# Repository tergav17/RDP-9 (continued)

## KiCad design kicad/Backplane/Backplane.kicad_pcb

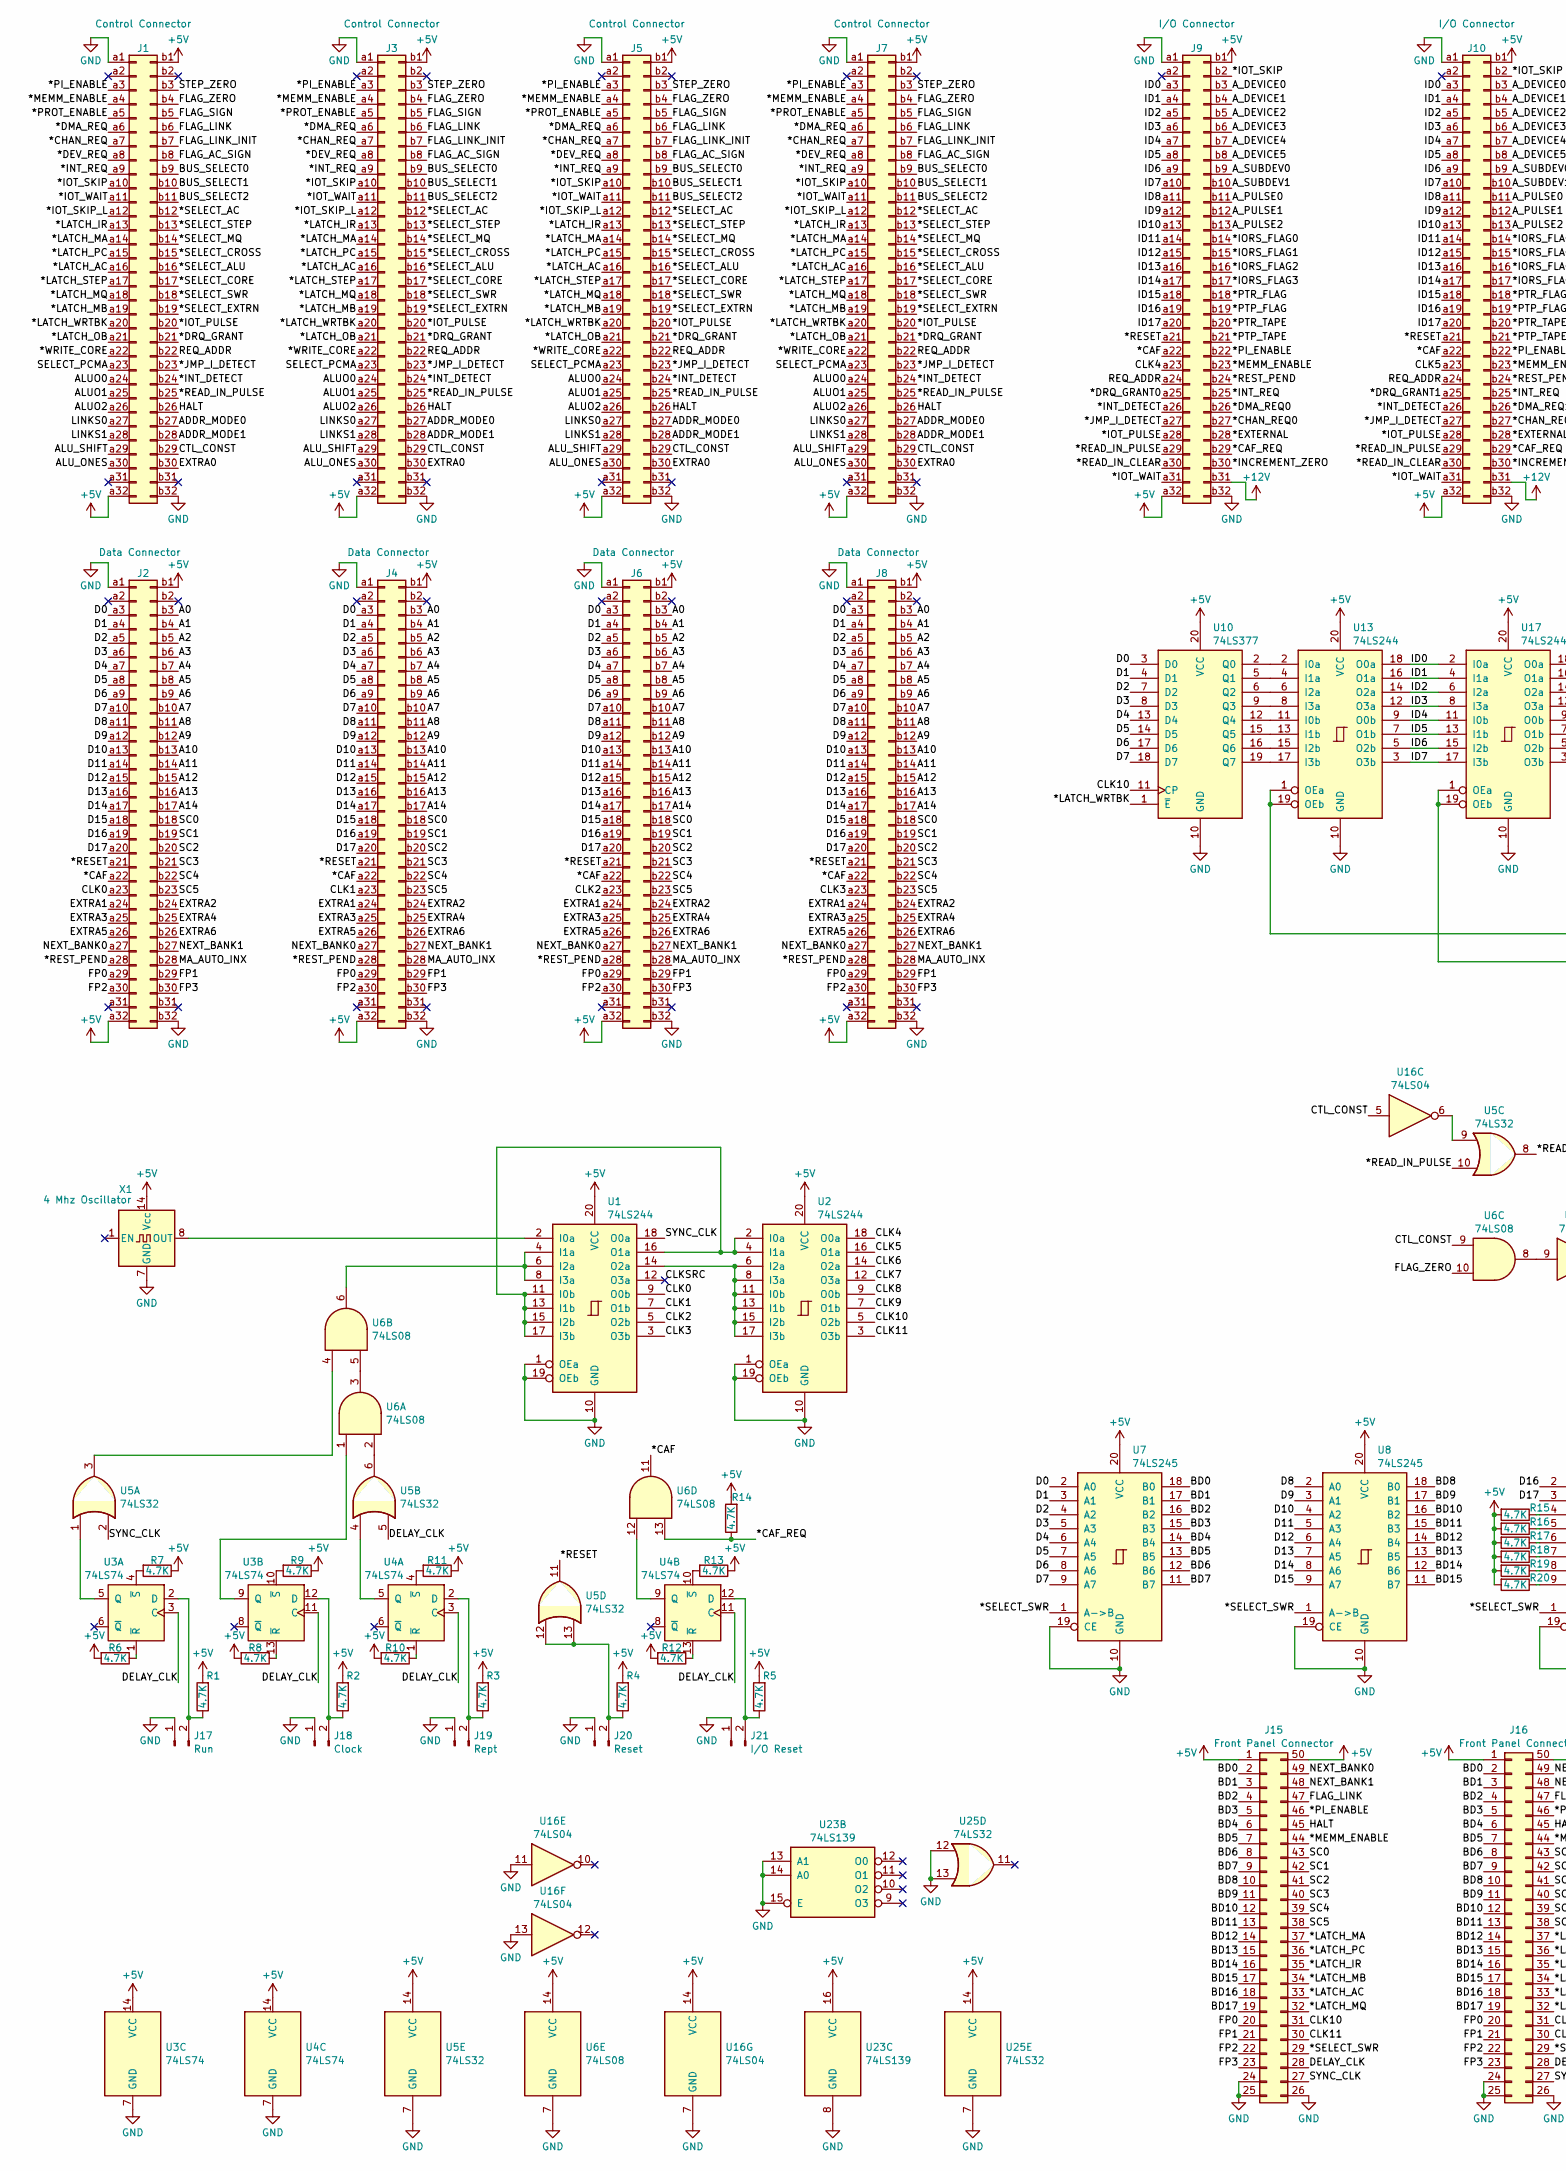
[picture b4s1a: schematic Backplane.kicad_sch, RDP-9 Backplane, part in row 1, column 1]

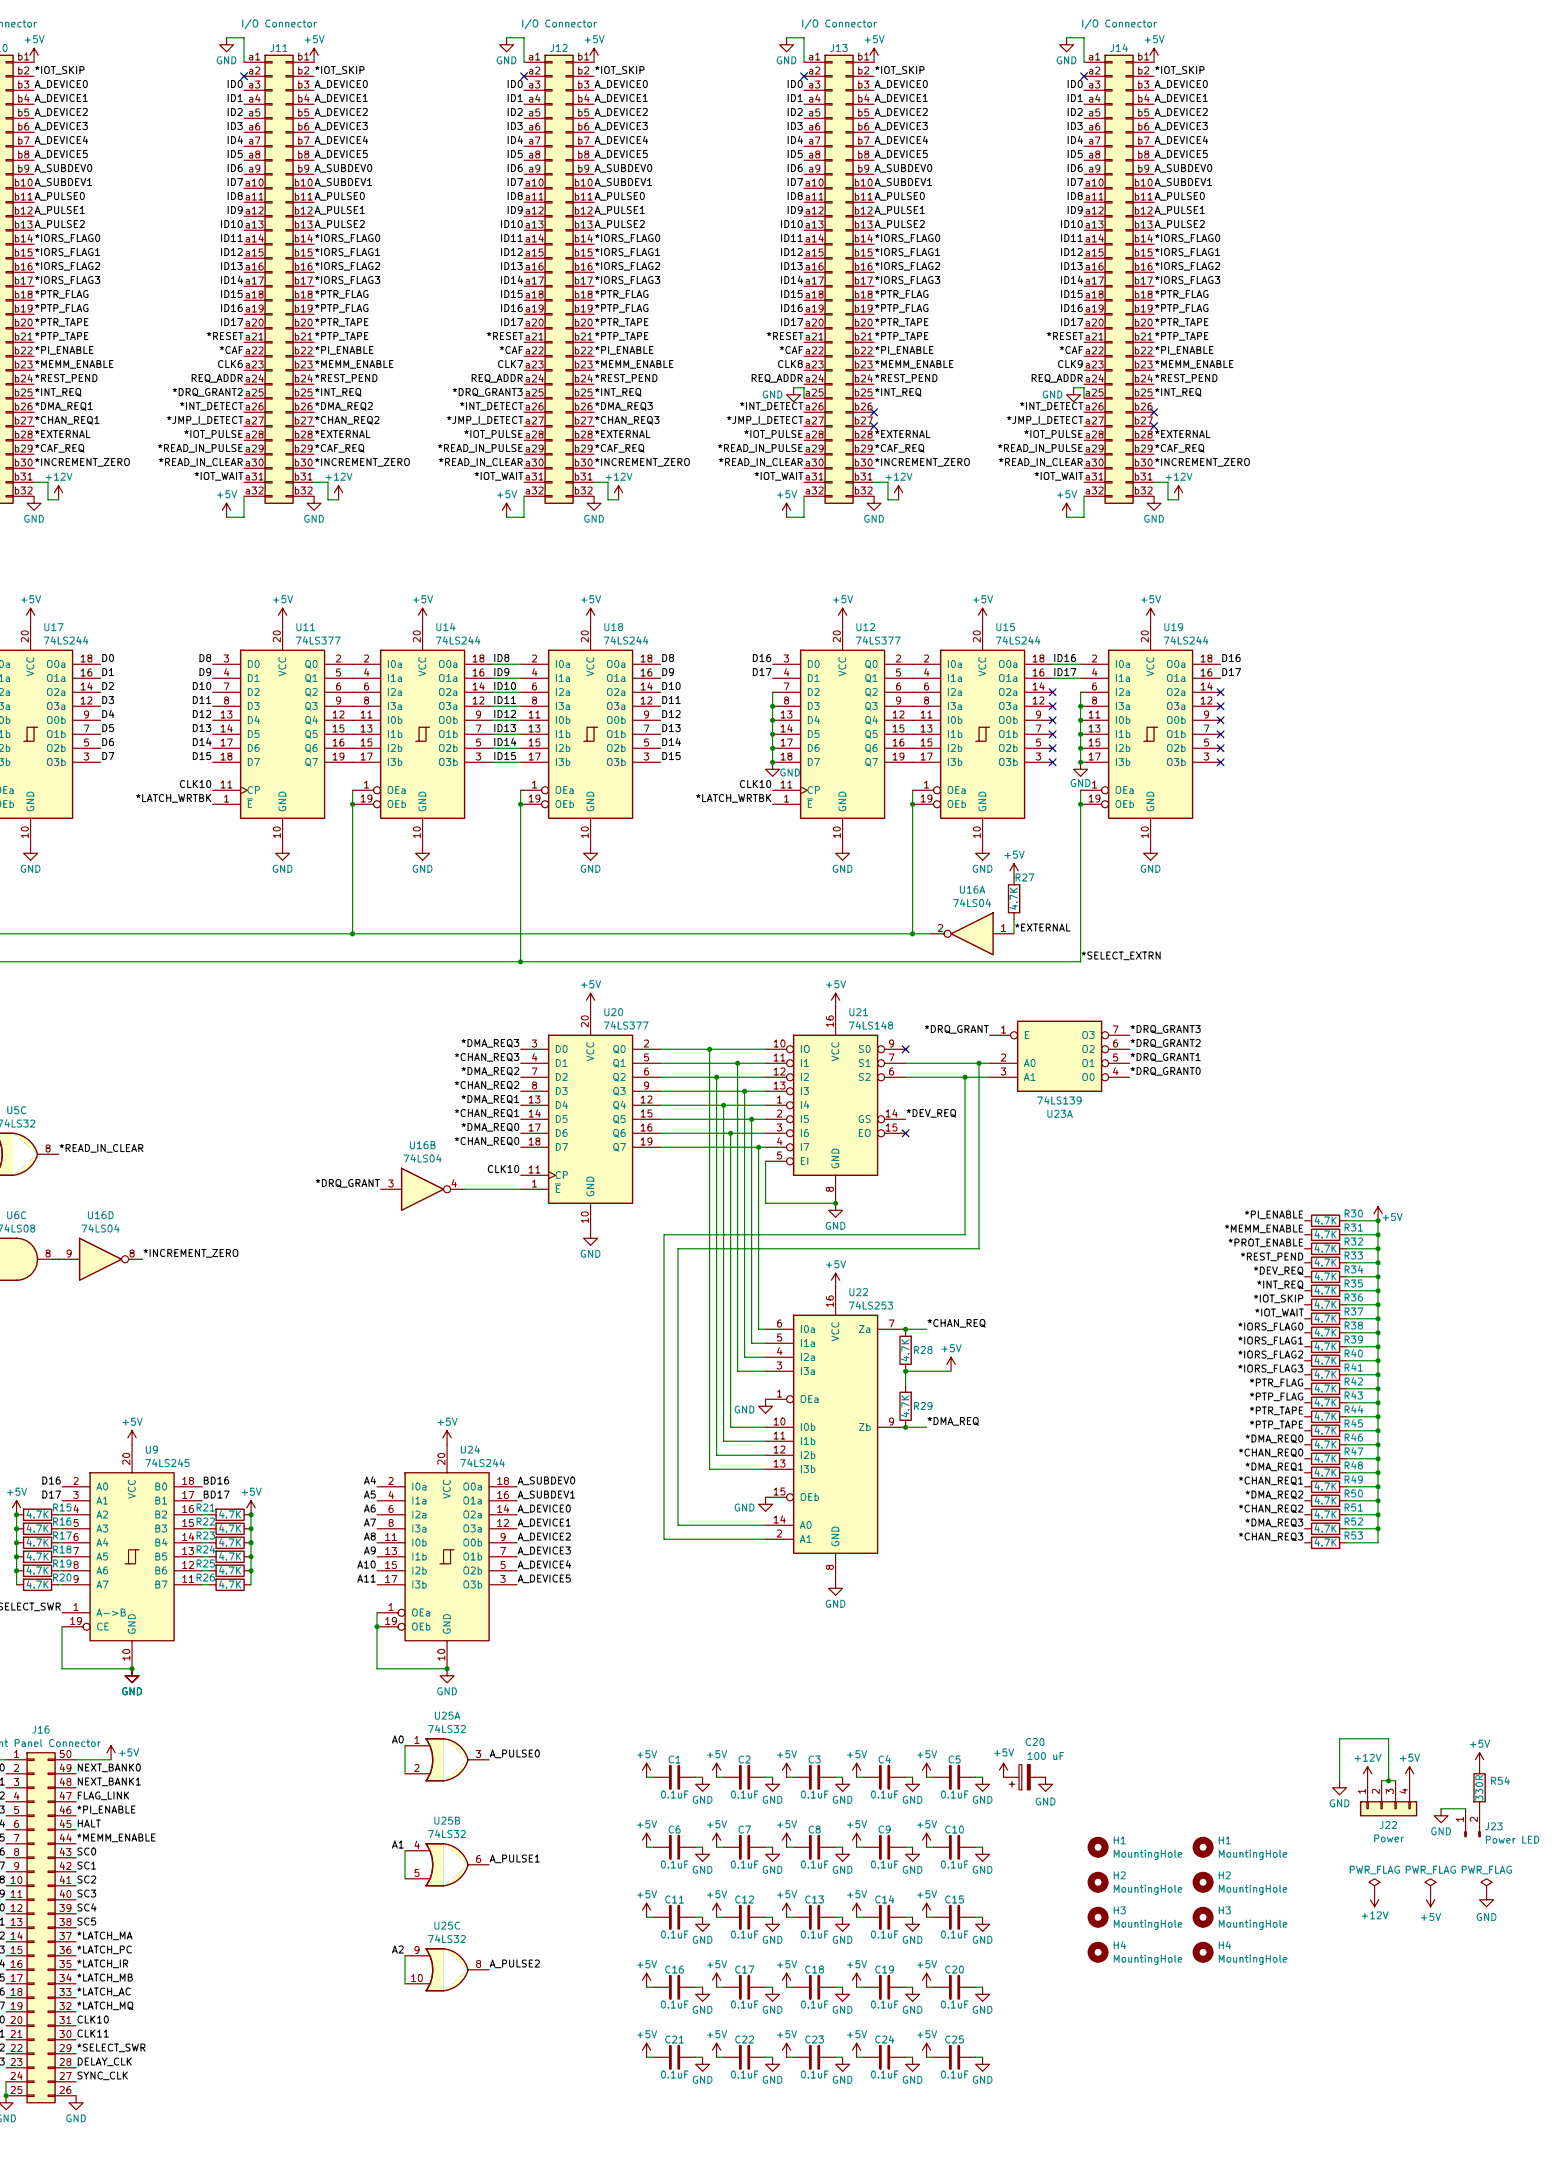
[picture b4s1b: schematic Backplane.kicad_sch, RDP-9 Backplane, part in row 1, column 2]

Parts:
C1, C2, C3, C4, C5, C6, C7, C8, C9, C10, C11, C12, C13, C14, C15, C16, C17, C18, C19, C20, C21, C22, C23, C24, C25: 0.1uF; C_Disc_D5.0mm_W2.5mm_P5.00mm
H1, H2, H3, H4: MountingHole; MountingHole_2.2mm_M2_Pad
J1, J3, J5, J7: Control Connector; DIN41612_B_2x32_Female_Vertical_THT
J2, J4, J6, J8: Data Connector; DIN41612_B_2x32_Female_Vertical_THT
J9, J10, J11, J12, J13, J14: I/O Connector; DIN41612_B_2x32_Female_Vertical_THT
J15, J16: Front Panel Connector; IDC-Header_2x25_P2.54mm_Vertical
J17: Run; PinHeader_1x02_P2.54mm_Vertical
J18: Clock; PinHeader_1x02_P2.54mm_Vertical
J19: Rept; PinHeader_1x02_P2.54mm_Vertical
J20: Reset; PinHeader_1x02_P2.54mm_Vertical
J21: I/O Reset; PinHeader_1x02_P2.54mm_Vertical
J22: Power; TE_MATE-N-LOK_350211-1_1x04_P5.08mm_Vertical
J23: Power LED; PinHeader_1x02_P2.54mm_Vertical
R1, R2, R3, R4, R5, R6, R7, R8, R9, R10, R11, R12, R13, R14, R15, R16, R17, R18, R19, R20, R21, R22, R23, R24, R25, R26, R27, R28, R29, R30, R31, R32, R33, R34, R35, R36, R37, R38, R39, R40, R41, R42, R43, R44, R45, R46, R47, R48, R49, R50, R51, R52, R53: 4.7K; R_Axial_DIN0207_L6.3mm_D2.5mm_P7.62mm_Horizontal
R54: 330R; R_Axial_DIN0207_L6.3mm_D2.5mm_P7.62mm_Horizontal
U1, U2, U13, U14, U15, U17, U18, U19, U24: 74LS244; DIP-20_W7.62mm
U3, U4: 74LS74; DIP-14_W7.62mm
U5, U25: 74LS32; DIP-14_W7.62mm
U6: 74LS08; DIP-14_W7.62mm
U7, U8, U9: 74LS245; DIP-20_W7.62mm
U10, U11, U12, U20: 74LS377; DIP-20_W7.62mm
U16: 74LS04; DIP-14_W7.62mm
U21: 74LS148; DIP-16_W7.62mm
U22: 74LS253; DIP-16_W7.62mm
U23: 74LS139; DIP-16_W7.62mm
X1: 4 Mhz Oscillator; Oscillator_DIP-14

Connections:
+5V: C1.1, C2.1, C3.1, C4.1, C5.1, C6.1, C7.1, C8.1, C9.1, C10.1, C11.1, C12.1, C13.1, C14.1, C15.1, C16.1, C17.1, C18.1, C19.1, C20.1, C21.1, C22.1, C23.1, C24.1, C25.1, J1.a32, J1.b1, J2.a32, J2.b1, J3.a32, J3.b1, J4.a32, J4.b1, J5.a32, J5.b1, J6.a32, J6.b1, J7.a32, J7.b1, J8.a32, J8.b1, J9.a32, J9.b1, J10.a32, J10.b1, J11.a32, J11.b1, J12.a32, J12.b1, J13.a32, J13.b1, J14.a32, J14.b1, J15.1, J15.50, J16.1, J16.50, J22.4, R1.2, R2.2, R3.2, R4.2, R5.2, R6.2, R7.1, R8.2, R9.1, R10.2, R11.1, R12.2, R13.1, R14.2, R15.2, R16.2, R17.2, R18.2, R19.2, R20.2, R21.1, R22.1, R23.1, R24.1, R25.1, R26.1, R27.2, R28.1, R29.2, R30.2, R31.2, R32.2, R33.2, R34.2, R35.2, R36.2, R37.2, R38.2, R39.2, R40.2, R41.2, R42.2, R43.2, R44.2, R45.2, R46.2, R47.2, R48.2, R49.2, R50.2, R51.2, R52.2, R53.2, R54.1, U1.20 (VCC), U2.20 (VCC), U3.14 (VCC), U4.14 (VCC), U5.14 (VCC), U6.14 (VCC), U7.20 (VCC), U8.20 (VCC), U9.20 (VCC), U10.20 (VCC), U11.20 (VCC), U12.20 (VCC), U13.20 (VCC), U14.20 (VCC), U15.20 (VCC), U16.14 (VCC), U17.20 (VCC), U18.20 (VCC), U19.20 (VCC), U20.20 (VCC), U21.16 (VCC), U22.16 (VCC), U23.16 (VCC), U24.20 (VCC), U25.14 (VCC), X1.14 (Vcc); also elsewhere on the board
+12V: J9.b31, J10.b31, J11.b31, J12.b31, J13.b31, J14.b31, J22.1
/*CAF: J2.a22, J4.a22, J6.a22, J8.a22, J9.a22, J10.a22, J11.a22, J12.a22, J13.a22, J14.a22, U6.11
/*CAF_REQ: J9.b29, J10.b29, J11.b29, J12.b29, J13.b29, J14.b29, R14.1, U6.13
/*CHAN_REQ: J1.a7, J3.a7, J5.a7, J7.a7, R28.2, U22.7 (Za)
/*CHAN_REQ0: J9.b27, R47.1, U20.18 (D7)
/*CHAN_REQ1: J10.b27, R49.1, U20.14 (D5)
/*CHAN_REQ2: J11.b27, R51.1, U20.8 (D3)
/*CHAN_REQ3: J12.b27, R53.1, U20.4 (D1)
/*DEV_REQ: J1.a8, J3.a8, J5.a8, J7.a8, R34.1, U21.14 (GS)
/*DMA_REQ: J1.a6, J3.a6, J5.a6, J7.a6, R29.1, U22.9 (Zb)
/*DMA_REQ0: J9.b26, R46.1, U20.17 (D6)
/*DMA_REQ1: J10.b26, R48.1, U20.13 (D4)
/*DMA_REQ2: J11.b26, R50.1, U20.7 (D2)
/*DMA_REQ3: J12.b26, R52.1, U20.3 (D0)
/*DRQ_GRANT: J1.b21, J3.b21, J5.b21, J7.b21, U16.3, U23.1 (E)
/*DRQ_GRANT0: J9.a25, U23.4 (O0)
/*DRQ_GRANT1: J10.a25, U23.5 (O1)
/*DRQ_GRANT2: J11.a25, U23.6 (O2)
/*DRQ_GRANT3: J12.a25, U23.7 (O3)
/*EXTERNAL: J9.b28, J10.b28, J11.b28, J12.b28, J13.b28, J14.b28, R27.1, U16.1
/*INCREMENT_ZERO: J9.b30, J10.b30, J11.b30, J12.b30, J13.b30, J14.b30, U16.8
/*INT_DETECT: J1.b24, J3.b24, J5.b24, J7.b24, J9.a26, J10.a26, J11.a26, J12.a26, J13.a26, J14.a26
/*INT_REQ: J1.a9, J3.a9, J5.a9, J7.a9, J9.b25, J10.b25, J11.b25, J12.b25, J13.b25, J14.b25, R35.1
/*IORS_FLAG0: J9.b14, J10.b14, J11.b14, J12.b14, J13.b14, J14.b14, R38.1
/*IORS_FLAG1: J9.b15, J10.b15, J11.b15, J12.b15, J13.b15, J14.b15, R39.1
/*IORS_FLAG2: J9.b16, J10.b16, J11.b16, J12.b16, J13.b16, J14.b16, R40.1
/*IORS_FLAG3: J9.b17, J10.b17, J11.b17, J12.b17, J13.b17, J14.b17, R41.1
/*IOT_PULSE: J1.b20, J3.b20, J5.b20, J7.b20, J9.a28, J10.a28, J11.a28, J12.a28, J13.a28, J14.a28
/*IOT_SKIP: J1.a10, J3.a10, J5.a10, J7.a10, J9.b2, J10.b2, J11.b2, J12.b2, J13.b2, J14.b2, R36.1
/*IOT_SKIP_L: J1.a12, J3.a12, J5.a12, J7.a12
/*IOT_WAIT: J1.a11, J3.a11, J5.a11, J7.a11, J9.a31, J10.a31, J11.a31, J12.a31, J13.a31, J14.a31, R37.1
/*JMP_I_DETECT: J1.b23, J3.b23, J5.b23, J7.b23, J9.a27, J10.a27, J11.a27, J12.a27, J13.a27, J14.a27
/*LATCH_AC: J1.a16, J3.a16, J5.a16, J7.a16, J15.33, J16.33
/*LATCH_IR: J1.a13, J3.a13, J5.a13, J7.a13, J15.35, J16.35
/*LATCH_MA: J1.a14, J3.a14, J5.a14, J7.a14, J15.37, J16.37
/*LATCH_MB: J1.a19, J3.a19, J5.a19, J7.a19, J15.34, J16.34
/*LATCH_MQ: J1.a18, J3.a18, J5.a18, J7.a18, J15.32, J16.32
/*LATCH_OB: J1.a21, J3.a21, J5.a21, J7.a21
/*LATCH_PC: J1.a15, J3.a15, J5.a15, J7.a15, J15.36, J16.36
/*LATCH_STEP: J1.a17, J3.a17, J5.a17, J7.a17
/*LATCH_WRTBK: J1.a20, J3.a20, J5.a20, J7.a20, U10.1 (~E), U11.1 (~E), U12.1 (~E)
/*MEMM_ENABLE: J1.a4, J3.a4, J5.a4, J7.a4, J9.b23, J10.b23, J11.b23, J12.b23, J13.b23, J14.b23, J15.44, J16.44, R31.1
/*PI_ENABLE: J1.a3, J3.a3, J5.a3, J7.a3, J9.b22, J10.b22, J11.b22, J12.b22, J13.b22, J14.b22, J15.46, J16.46, R30.1
/*PROT_ENABLE: J1.a5, J3.a5, J5.a5, J7.a5, R32.1
/*PTP_FLAG: J9.b19, J10.b19, J11.b19, J12.b19, J13.b19, J14.b19, R43.1
/*PTP_TAPE: J9.b21, J10.b21, J11.b21, J12.b21, J13.b21, J14.b21, R45.1
/*PTR_FLAG: J9.b18, J10.b18, J11.b18, J12.b18, J13.b18, J14.b18, R42.1
/*PTR_TAPE: J9.b20, J10.b20, J11.b20, J12.b20, J13.b20, J14.b20, R44.1
/*READ_IN_CLEAR: J9.a30, J10.a30, J11.a30, J12.a30, J13.a30, J14.a30, U5.8
/*READ_IN_PULSE: J1.b25, J3.b25, J5.b25, J7.b25, J9.a29, J10.a29, J11.a29, J12.a29, J13.a29, J14.a29, U5.10
/*RESET: J2.a21, J4.a21, J6.a21, J8.a21, J9.a21, J10.a21, J11.a21, J12.a21, J13.a21, J14.a21, U5.11
/*REST_PEND: J2.a28, J4.a28, J6.a28, J8.a28, J9.b24, J10.b24, J11.b24, J12.b24, J13.b24, J14.b24, R33.1
/*SELECT_AC: J1.b12, J3.b12, J5.b12, J7.b12
/*SELECT_ALU: J1.b16, J3.b16, J5.b16, J7.b16
/*SELECT_CORE: J1.b17, J3.b17, J5.b17, J7.b17
/*SELECT_CROSS: J1.b15, J3.b15, J5.b15, J7.b15
/*SELECT_EXTRN: J1.b19, J3.b19, J5.b19, J7.b19, U17.1 (OEa), U17.19 (OEb), U18.1 (OEa), U18.19 (OEb), U19.1 (OEa), U19.19 (OEb)
/*SELECT_MQ: J1.b14, J3.b14, J5.b14, J7.b14
/*SELECT_STEP: J1.b13, J3.b13, J5.b13, J7.b13
/*SELECT_SWR: J1.b18, J3.b18, J5.b18, J7.b18, J15.29, J16.29, U7.1 (A->B), U8.1 (A->B), U9.1 (A->B)
/*WRITE_CORE: J1.a22, J3.a22, J5.a22, J7.a22
/A0: J2.b3, J4.b3, J6.b3, J8.b3, U25.1, U25.2
/A1: J2.b4, J4.b4, J6.b4, J8.b4, U25.4, U25.5
/A2: J2.b5, J4.b5, J6.b5, J8.b5, U25.9, U25.10
/A3: J2.b6, J4.b6, J6.b6, J8.b6
/A4: J2.b7, J4.b7, J6.b7, J8.b7, U24.2 (I0a)
/A5: J2.b8, J4.b8, J6.b8, J8.b8, U24.4 (I1a)
/A6: J2.b9, J4.b9, J6.b9, J8.b9, U24.6 (I2a)
/A7: J2.b10, J4.b10, J6.b10, J8.b10, U24.8 (I3a)
/A8: J2.b11, J4.b11, J6.b11, J8.b11, U24.11 (I0b)
/A9: J2.b12, J4.b12, J6.b12, J8.b12, U24.13 (I1b)
/A10: J2.b13, J4.b13, J6.b13, J8.b13, U24.15 (I2b)
/A11: J2.b14, J4.b14, J6.b14, J8.b14, U24.17 (I3b)
/A12: J2.b15, J4.b15, J6.b15, J8.b15
/A13: J2.b16, J4.b16, J6.b16, J8.b16
/A14: J2.b17, J4.b17, J6.b17, J8.b17
/ADDR_MODE0: J1.b27, J3.b27, J5.b27, J7.b27
/ADDR_MODE1: J1.b28, J3.b28, J5.b28, J7.b28
/ALUO0: J1.a24, J3.a24, J5.a24, J7.a24
/ALUO1: J1.a25, J3.a25, J5.a25, J7.a25
/ALUO2: J1.a26, J3.a26, J5.a26, J7.a26
/ALU_ONES: J1.a30, J3.a30, J5.a30, J7.a30
/ALU_SHIFT: J1.a29, J3.a29, J5.a29, J7.a29
/A_DEVICE0: J9.b3, J10.b3, J11.b3, J12.b3, J13.b3, J14.b3, U24.14 (O2a)
/A_DEVICE1: J9.b4, J10.b4, J11.b4, J12.b4, J13.b4, J14.b4, U24.12 (O3a)
/A_DEVICE2: J9.b5, J10.b5, J11.b5, J12.b5, J13.b5, J14.b5, U24.9 (O0b)
/A_DEVICE3: J9.b6, J10.b6, J11.b6, J12.b6, J13.b6, J14.b6, U24.7 (O1b)
/A_DEVICE4: J9.b7, J10.b7, J11.b7, J12.b7, J13.b7, J14.b7, U24.5 (O2b)
/A_DEVICE5: J9.b8, J10.b8, J11.b8, J12.b8, J13.b8, J14.b8, U24.3 (O3b)
/A_PULSE0: J9.b11, J10.b11, J11.b11, J12.b11, J13.b11, J14.b11, U25.3
/A_PULSE1: J9.b12, J10.b12, J11.b12, J12.b12, J13.b12, J14.b12, U25.6
/A_PULSE2: J9.b13, J10.b13, J11.b13, J12.b13, J13.b13, J14.b13, U25.8
/A_SUBDEV0: J9.b9, J10.b9, J11.b9, J12.b9, J13.b9, J14.b9, U24.18 (O0a)
/A_SUBDEV1: J9.b10, J10.b10, J11.b10, J12.b10, J13.b10, J14.b10, U24.16 (O1a)
/BD0: J15.2, J16.2, U7.18 (B0)
/BD1: J15.3, J16.3, U7.17 (B1)
/BD2: J15.4, J16.4, U7.16 (B2)
/BD3: J15.5, J16.5, U7.15 (B3)
/BD4: J15.6, J16.6, U7.14 (B4)
/BD5: J15.7, J16.7, U7.13 (B5)
/BD6: J15.8, J16.8, U7.12 (B6)
/BD7: J15.9, J16.9, U7.11 (B7)
/BD8: J15.10, J16.10, U8.18 (B0)
/BD9: J15.11, J16.11, U8.17 (B1)
/BD10: J15.12, J16.12, U8.16 (B2)
/BD11: J15.13, J16.13, U8.15 (B3)
/BD12: J15.14, J16.14, U8.14 (B4)
/BD13: J15.15, J16.15, U8.13 (B5)
/BD14: J15.16, J16.16, U8.12 (B6)
/BD15: J15.17, J16.17, U8.11 (B7)
/BD16: J15.18, J16.18, U9.18 (B0)
/BD17: J15.19, J16.19, U9.17 (B1)
/BUS_SELECT0: J1.b9, J3.b9, J5.b9, J7.b9
/BUS_SELECT1: J1.b10, J3.b10, J5.b10, J7.b10
/BUS_SELECT2: J1.b11, J3.b11, J5.b11, J7.b11
/CLK0: J2.a23, U1.9 (O0b)
/CLK1: J4.a23, U1.7 (O1b)
/CLK2: J6.a23, U1.5 (O2b)
/CLK3: J8.a23, U1.3 (O3b)
/CLK4: J9.a23, U2.18 (O0a)
/CLK5: J10.a23, U2.16 (O1a)
/CLK6: J11.a23, U2.14 (O2a)
/CLK7: J12.a23, U2.12 (O3a)
/CLK8: J13.a23, U2.9 (O0b)
/CLK9: J14.a23, U2.7 (O1b)
/CLK10: J15.31, J16.31, U2.5 (O2b), U10.11 (CP), U11.11 (CP), U12.11 (CP), U20.11 (CP)
/CLK11: J15.30, J16.30, U2.3 (O3b)
/CLKSRC: U1.12 (O3a)
/CTL_CONST: J1.b29, J3.b29, J5.b29, J7.b29, U6.9, U16.5
/D0: J2.a3, J4.a3, J6.a3, J8.a3, U7.2 (A0), U10.3 (D0), U17.18 (O0a)
/D1: J2.a4, J4.a4, J6.a4, J8.a4, U7.3 (A1), U10.4 (D1), U17.16 (O1a)
/D2: J2.a5, J4.a5, J6.a5, J8.a5, U7.4 (A2), U10.7 (D2), U17.14 (O2a)
/D3: J2.a6, J4.a6, J6.a6, J8.a6, U7.5 (A3), U10.8 (D3), U17.12 (O3a)
/D4: J2.a7, J4.a7, J6.a7, J8.a7, U7.6 (A4), U10.13 (D4), U17.9 (O0b)
/D5: J2.a8, J4.a8, J6.a8, J8.a8, U7.7 (A5), U10.14 (D5), U17.7 (O1b)
/D6: J2.a9, J4.a9, J6.a9, J8.a9, U7.8 (A6), U10.17 (D6), U17.5 (O2b)
/D7: J2.a10, J4.a10, J6.a10, J8.a10, U7.9 (A7), U10.18 (D7), U17.3 (O3b)
/D8: J2.a11, J4.a11, J6.a11, J8.a11, U8.2 (A0), U11.3 (D0), U18.18 (O0a)
/D9: J2.a12, J4.a12, J6.a12, J8.a12, U8.3 (A1), U11.4 (D1), U18.16 (O1a)
/D10: J2.a13, J4.a13, J6.a13, J8.a13, U8.4 (A2), U11.7 (D2), U18.14 (O2a)
/D11: J2.a14, J4.a14, J6.a14, J8.a14, U8.5 (A3), U11.8 (D3), U18.12 (O3a)
/D12: J2.a15, J4.a15, J6.a15, J8.a15, U8.6 (A4), U11.13 (D4), U18.9 (O0b)
/D13: J2.a16, J4.a16, J6.a16, J8.a16, U8.7 (A5), U11.14 (D5), U18.7 (O1b)
/D14: J2.a17, J4.a17, J6.a17, J8.a17, U8.8 (A6), U11.17 (D6), U18.5 (O2b)
/D15: J2.a18, J4.a18, J6.a18, J8.a18, U8.9 (A7), U11.18 (D7), U18.3 (O3b)
/D16: J2.a19, J4.a19, J6.a19, J8.a19, U9.2 (A0), U12.3 (D0), U19.18 (O0a)
/D17: J2.a20, J4.a20, J6.a20, J8.a20, U9.3 (A1), U12.4 (D1), U19.16 (O1a)
/DELAY_CLK: J15.28, J16.28, U3.3 (C), U3.11 (C), U4.3 (C), U4.11 (C), U5.5
/EXTRA0: J1.b30, J3.b30, J5.b30, J7.b30
/EXTRA1: J2.a24, J4.a24, J6.a24, J8.a24
/EXTRA2: J2.b24, J4.b24, J6.b24, J8.b24
/EXTRA3: J2.a25, J4.a25, J6.a25, J8.a25
/EXTRA4: J2.b25, J4.b25, J6.b25, J8.b25
/EXTRA5: J2.a26, J4.a26, J6.a26, J8.a26
/EXTRA6: J2.b26, J4.b26, J6.b26, J8.b26
/FLAG_AC_SIGN: J1.b8, J3.b8, J5.b8, J7.b8
/FLAG_LINK: J1.b6, J3.b6, J5.b6, J7.b6, J15.47, J16.47
/FLAG_LINK_INIT: J1.b7, J3.b7, J5.b7, J7.b7
/FLAG_SIGN: J1.b5, J3.b5, J5.b5, J7.b5
/FLAG_ZERO: J1.b4, J3.b4, J5.b4, J7.b4, U6.10
/FP0: J2.a29, J4.a29, J6.a29, J8.a29, J15.20, J16.20
/FP1: J2.b29, J4.b29, J6.b29, J8.b29, J15.21, J16.21
/FP2: J2.a30, J4.a30, J6.a30, J8.a30, J15.22, J16.22
/FP3: J2.b30, J4.b30, J6.b30, J8.b30, J15.23, J16.23
/HALT: J1.b26, J3.b26, J5.b26, J7.b26, J15.45, J16.45
/ID0: J9.a3, J10.a3, J11.a3, J12.a3, J13.a3, J14.a3, U13.18 (O0a), U17.2 (I0a)
/ID1: J9.a4, J10.a4, J11.a4, J12.a4, J13.a4, J14.a4, U13.16 (O1a), U17.4 (I1a)
/ID2: J9.a5, J10.a5, J11.a5, J12.a5, J13.a5, J14.a5, U13.14 (O2a), U17.6 (I2a)
/ID3: J9.a6, J10.a6, J11.a6, J12.a6, J13.a6, J14.a6, U13.12 (O3a), U17.8 (I3a)
/ID4: J9.a7, J10.a7, J11.a7, J12.a7, J13.a7, J14.a7, U13.9 (O0b), U17.11 (I0b)
/ID5: J9.a8, J10.a8, J11.a8, J12.a8, J13.a8, J14.a8, U13.7 (O1b), U17.13 (I1b)
/ID6: J9.a9, J10.a9, J11.a9, J12.a9, J13.a9, J14.a9, U13.5 (O2b), U17.15 (I2b)
/ID7: J9.a10, J10.a10, J11.a10, J12.a10, J13.a10, J14.a10, U13.3 (O3b), U17.17 (I3b)
/ID8: J9.a11, J10.a11, J11.a11, J12.a11, J13.a11, J14.a11, U14.18 (O0a), U18.2 (I0a)
/ID9: J9.a12, J10.a12, J11.a12, J12.a12, J13.a12, J14.a12, U14.16 (O1a), U18.4 (I1a)
/ID10: J9.a13, J10.a13, J11.a13, J12.a13, J13.a13, J14.a13, U14.14 (O2a), U18.6 (I2a)
/ID11: J9.a14, J10.a14, J11.a14, J12.a14, J13.a14, J14.a14, U14.12 (O3a), U18.8 (I3a)
/ID12: J9.a15, J10.a15, J11.a15, J12.a15, J13.a15, J14.a15, U14.9 (O0b), U18.11 (I0b)
/ID13: J9.a16, J10.a16, J11.a16, J12.a16, J13.a16, J14.a16, U14.7 (O1b), U18.13 (I1b)
/ID14: J9.a17, J10.a17, J11.a17, J12.a17, J13.a17, J14.a17, U14.5 (O2b), U18.15 (I2b)
/ID15: J9.a18, J10.a18, J11.a18, J12.a18, J13.a18, J14.a18, U14.3 (O3b), U18.17 (I3b)
/ID16: J9.a19, J10.a19, J11.a19, J12.a19, J13.a19, J14.a19, U15.18 (O0a), U19.2 (I0a)
/ID17: J9.a20, J10.a20, J11.a20, J12.a20, J13.a20, J14.a20, U15.16 (O1a), U19.4 (I1a)
/LINKS0: J1.a27, J3.a27, J5.a27, J7.a27
/LINKS1: J1.a28, J3.a28, J5.a28, J7.a28
/MA_AUTO_INX: J2.b28, J4.b28, J6.b28, J8.b28
/NEXT_BANK0: J2.a27, J4.a27, J6.a27, J8.a27, J15.49, J16.49
/NEXT_BANK1: J2.b27, J4.b27, J6.b27, J8.b27, J15.48, J16.48
/REQ_ADDR: J1.b22, J3.b22, J5.b22, J7.b22, J9.a24, J10.a24, J11.a24, J12.a24, J13.a24, J14.a24
/SC0: J2.b18, J4.b18, J6.b18, J8.b18, J15.43, J16.43
/SC1: J2.b19, J4.b19, J6.b19, J8.b19, J15.42, J16.42
/SC2: J2.b20, J4.b20, J6.b20, J8.b20, J15.41, J16.41
/SC3: J2.b21, J4.b21, J6.b21, J8.b21, J15.40, J16.40
/SC4: J2.b22, J4.b22, J6.b22, J8.b22, J15.39, J16.39
/SC5: J2.b23, J4.b23, J6.b23, J8.b23, J15.38, J16.38
/SELECT_PCMA: J1.a23, J3.a23, J5.a23, J7.a23
/STEP_ZERO: J1.b3, J3.b3, J5.b3, J7.b3
/SYNC_CLK: J15.27, J16.27, U1.18 (O0a), U5.2
GND: C1.2, C2.2, C3.2, C4.2, C5.2, C6.2, C7.2, C8.2, C9.2, C10.2, C11.2, C12.2, C13.2, C14.2, C15.2, C16.2, C17.2, C18.2, C19.2, C20.2, C21.2, C22.2, C23.2, C24.2, C25.2, J1.a1, J1.b32, J2.a1, J2.b32, J3.a1, J3.b32, J4.a1, J4.b32, J5.a1, J5.b32, J6.a1, J6.b32, J7.a1, J7.b32, J8.a1, J8.b32, J9.a1, J9.b32, J10.a1, J10.b32, J11.a1, J11.b32, J12.a1, J12.b32, J13.a1, J13.a25, J13.b32, J14.a1, J14.a25, J14.b32, J15.24, J15.25, J15.26, J16.24, J16.25, J16.26, J17.1, J18.1, J19.1, J20.1, J21.1, J22.2, J22.3, J23.1, U1.1 (OEa), U1.10 (GND), U1.19 (OEb), U2.1 (OEa), U2.10 (GND), U2.19 (OEb), U3.7 (GND), U4.7 (GND), U5.7 (GND), U6.7 (GND), U7.10 (GND), U7.19 (CE), U8.10 (GND), U8.19 (CE), U9.10 (GND), U9.19 (CE), U10.10 (GND), U11.10 (GND), U12.7 (D2), U12.8 (D3), U12.10 (GND), U12.13 (D4), U12.14 (D5), U12.17 (D6), U12.18 (D7), U13.10 (GND), U14.10 (GND), U15.10 (GND), U16.7 (GND), U16.11, U16.13, U17.10 (GND), U18.10 (GND), U19.6 (I2a), U19.8 (I3a), U19.10 (GND), U19.11 (I0b), U19.13 (I1b), U19.15 (I2b), U19.17 (I3b), U20.10 (GND), U21.5 (EI), U21.8 (GND), U22.1 (OEa), U22.8 (GND), U22.15 (OEb), U23.8 (GND), U23.13 (A1), U23.14 (A0), U23.15 (E), U24.1 (OEa), U24.10 (GND), U24.19 (OEb), U25.7 (GND), U25.12, U25.13, X1.7 (GND); also elsewhere on the board
unnamed: J17.2, R1.1, U3.2 (D)
unnamed: J18.2, R2.1, U3.12 (D)
unnamed: J19.2, R3.1, U4.2 (D)
unnamed: J20.2, R4.1, U5.12, U5.13
unnamed: J21.2, R5.1, U4.12 (D)
unnamed: J23.2, R54.2
unnamed: U1.2 (I0a), X1.8 (OUT)
unnamed: U1.11 (I0b), U1.13 (I1b), U1.15 (I2b), U1.16 (O1a), U1.17 (I3b), U2.2 (I0a), U2.4 (I1a)
unnamed: U1.4 (I1a), U1.6 (I2a), U1.8 (I3a), U6.6
unnamed: U1.14 (O2a), U2.6 (I2a), U2.8 (I3a), U2.11 (I0b), U2.13 (I1b), U2.15 (I2b), U2.17 (I3b)
unnamed: U3.5 (Q), U5.1
unnamed: R6.1, U3.1 (~R)
unnamed: R7.2, U3.4 (~S)
unnamed: U3.9 (Q), U6.1
unnamed: R8.1, U3.13 (~R)
unnamed: R9.2, U3.10 (~S)
unnamed: U4.5 (Q), U5.4
unnamed: R10.1, U4.1 (~R)
unnamed: R11.2, U4.4 (~S)
unnamed: U4.9 (Q), U6.12
unnamed: R12.1, U4.13 (~R)
unnamed: R13.2, U4.10 (~S)
unnamed: U5.3, U6.4
unnamed: U5.6, U6.2
unnamed: U6.3, U6.5
unnamed: R15.1, U9.4 (A2)
unnamed: R16.1, U9.5 (A3)
unnamed: R17.1, U9.6 (A4)
unnamed: R18.1, U9.7 (A5)
unnamed: R19.1, U9.8 (A6)
unnamed: R20.1, U9.9 (A7)
unnamed: R21.2, U9.16 (B2)
unnamed: R22.2, U9.15 (B3)
unnamed: R23.2, U9.14 (B4)
unnamed: R24.2, U9.13 (B5)
unnamed: R25.2, U9.12 (B6)
unnamed: R26.2, U9.11 (B7)
unnamed: U10.2 (Q0), U13.2 (I0a)
unnamed: U10.5 (Q1), U13.4 (I1a)
unnamed: U10.6 (Q2), U13.6 (I2a)
unnamed: U10.9 (Q3), U13.8 (I3a)
unnamed: U10.12 (Q4), U13.11 (I0b)
unnamed: U10.15 (Q5), U13.13 (I1b)
unnamed: U10.16 (Q6), U13.15 (I2b)
unnamed: U10.19 (Q7), U13.17 (I3b)
unnamed: U11.2 (Q0), U14.2 (I0a)
unnamed: U11.5 (Q1), U14.4 (I1a)
unnamed: U11.6 (Q2), U14.6 (I2a)
unnamed: U11.9 (Q3), U14.8 (I3a)
unnamed: U11.12 (Q4), U14.11 (I0b)
unnamed: U11.15 (Q5), U14.13 (I1b)
unnamed: U11.16 (Q6), U14.15 (I2b)
unnamed: U11.19 (Q7), U14.17 (I3b)
unnamed: U12.2 (Q0), U15.2 (I0a)
unnamed: U12.5 (Q1), U15.4 (I1a)
unnamed: U12.6 (Q2), U15.6 (I2a)
unnamed: U12.9 (Q3), U15.8 (I3a)
unnamed: U12.12 (Q4), U15.11 (I0b)
unnamed: U12.15 (Q5), U15.13 (I1b)
unnamed: U12.16 (Q6), U15.15 (I2b)
unnamed: U12.19 (Q7), U15.17 (I3b)
unnamed: U13.1 (OEa), U13.19 (OEb), U14.1 (OEa), U14.19 (OEb), U15.1 (OEa), U15.19 (OEb), U16.2
unnamed: U5.9, U16.6
unnamed: U6.8, U16.9
unnamed: U20.2 (Q0), U21.10 (IO), U22.13 (I3b)
unnamed: U20.5 (Q1), U21.11 (I1), U22.3 (I3a)
unnamed: U20.6 (Q2), U21.12 (I2), U22.12 (I2b)
unnamed: U20.9 (Q3), U21.13 (I3), U22.4 (I2a)
unnamed: U20.12 (Q4), U21.1 (I4), U22.11 (I1b)
unnamed: U20.15 (Q5), U21.2 (I5), U22.5 (I1a)
unnamed: U20.16 (Q6), U21.3 (I6), U22.10 (I0b)
unnamed: U20.19 (Q7), U21.4 (I7), U22.6 (I0a)
unnamed: U16.4, U20.1 (~E)
unnamed: U21.7 (S1), U22.14 (A0), U23.2 (A0)
unnamed: U21.6 (S2), U22.2 (A1), U23.3 (A1)

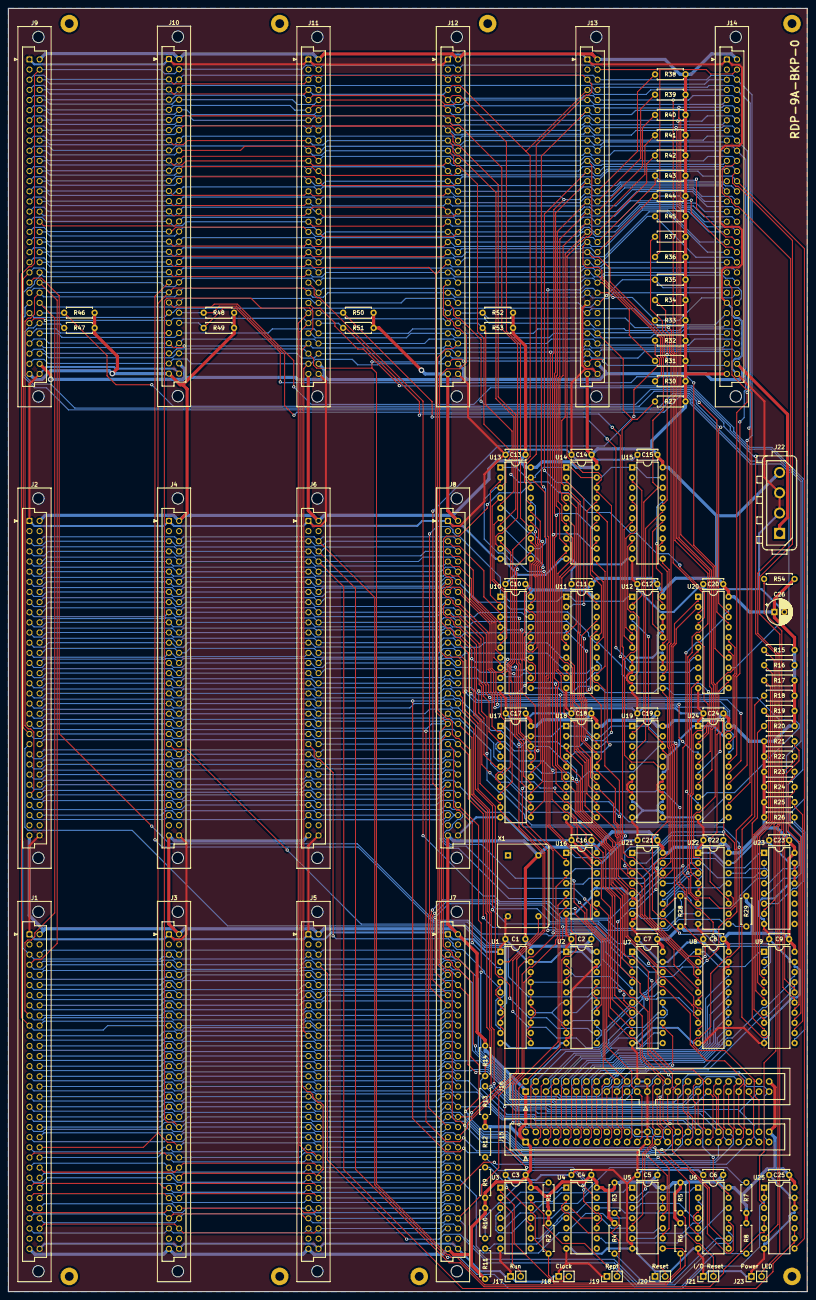
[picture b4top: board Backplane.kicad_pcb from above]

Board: 2 copper layers, 200.0 x 321.3 mm, 137 parts (0 on the bottom side), 274 nets.

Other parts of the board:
C26: 100 uF; CP_Radial_D6.3mm_P2.50mm
H5, H6, H7, H8: MountingHole; MountingHole_2.2mm_M2_Pad

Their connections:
+5V: C26.1; also elsewhere on the board
GND: C26.2; also elsewhere on the board
